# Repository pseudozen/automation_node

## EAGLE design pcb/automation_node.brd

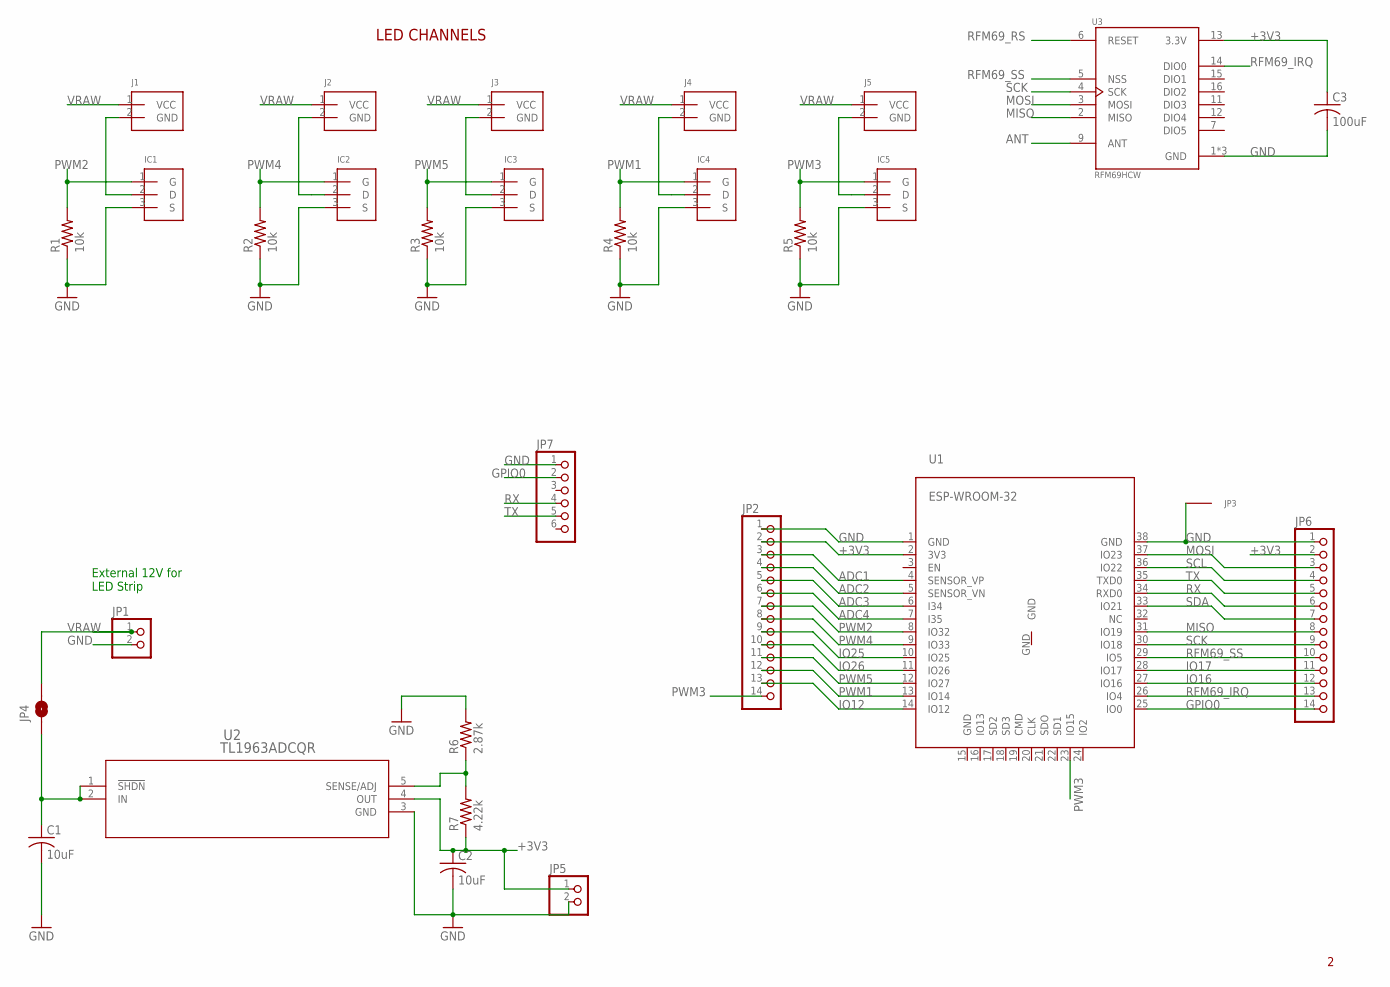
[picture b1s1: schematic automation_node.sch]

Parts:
C1, C2: 10uF; C0805
C3: 100uF; C0805
IC1, IC2, IC3, IC4, IC5: POWER_FET
J1, J2, J3, J4, J5: POWER-VIAS; 2CT-VIAS
JP1, JP5: PINHD-1X2; 1X02
JP2, JP6: PINHD-1X14; 1X14
JP3: PROTO_VIA_COMPACT; PROTO_VIA
JP4: JUMPER-SMT_2_NO_SILK; SMT-JUMPER_2_NO_SILK
JP7: PINHD-1X6; 1X06
R1, R2, R3, R4, R5: 10k; R0805
R6: 2.87k; R0805
R7: 4.22k; R0805
U1: ESP-WROOM-32
U2: TL1963ADCQR; DCQ6
U3: RFM69HCW; MOD_COM-13909

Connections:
+3V3: C2.1, C3.1, JP2.2, JP5.1, JP6.2, R7.1, U1.2 (3V3), U2.4 (OUT), U3.13 (3.3V)
ADC1: JP2.3, U1.4 (SENSOR_VP)
ADC2: JP2.4, U1.5 (SENSOR_VN)
ADC3: JP2.5, U1.6 (I34)
ADC4: JP2.6, U1.7 (I35)
ANT: U3.9 (ANT)
GND: C1.2, C2.2, C3.2, IC1.3 (S), IC2.3 (S), IC3.3 (S), IC4.3 (S), IC5.3 (S), JP1.2, JP2.1, JP3.1, JP5.2, JP6.1, JP7.1, R1.1, R2.1, R3.1, R4.1, R5.1, R6.2, U1.1 (GND), U1.38 (GND), U2.3 (GND), U3.1 (GND), U3.8 (GND), U3.10 (GND)
GPIO0: JP6.14, JP7.2, U1.25 (IO0)
IO12: JP2.13, U1.14 (IO12)
IO16: JP6.12, U1.27 (IO16)
IO17: JP6.11, U1.28 (IO17)
IO25: JP2.9, U1.10 (IO25)
IO26: JP2.10, U1.11 (IO26)
MISO: JP6.8, U1.31 (IO19), U3.2 (MISO)
MOSI: JP6.3, U1.37 (IO23), U3.3 (MOSI)
unnamed: IC1.2 (D), J1.2 (GND)
unnamed: IC2.2 (D), J2.2 (GND)
unnamed: IC3.2 (D), J3.2 (GND)
unnamed: IC4.2 (D), J4.2 (GND)
unnamed: IC5.2 (D), J5.2 (GND)
PWM1: IC4.1 (G), JP2.12, R4.2, U1.13 (IO14)
PWM2: IC1.1 (G), JP2.7, R1.2, U1.8 (IO32)
PWM3: IC5.1 (G), JP2.14, R5.2, U1.23 (IO15)
PWM4: IC2.1 (G), JP2.8, R2.2, U1.9 (IO33)
PWM5: IC3.1 (G), JP2.11, R3.2, U1.12 (IO27)
RFM69_IRQ: JP6.13, U1.26 (IO4), U3.14 (DIO0)
RFM69_RS: U3.6 (RESET)
RFM69_SS: JP6.10, U1.29 (IO5), U3.5 (NSS)
RX: JP6.6, JP7.4, U1.34 (RXD0)
SCK: JP6.9, U1.30 (IO18), U3.4 (SCK)
SCL: JP6.4, U1.36 (IO22)
SDA: JP6.7, U1.33 (IO21)
SHDN: C1.1, JP4.1, U2.1 (!SHDN), U2.2 (IN)
TX: JP6.5, JP7.5, U1.35 (TXD0)
U2_ADJ: R6.1, R7.2, U2.5 (SENSE/ADJ)
VRAW: J1.1 (VCC), J2.1 (VCC), J3.1 (VCC), J4.1 (VCC), J5.1 (VCC), JP1.1, JP4.2

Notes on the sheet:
LED CHANNELS
External 12V for LED Strip

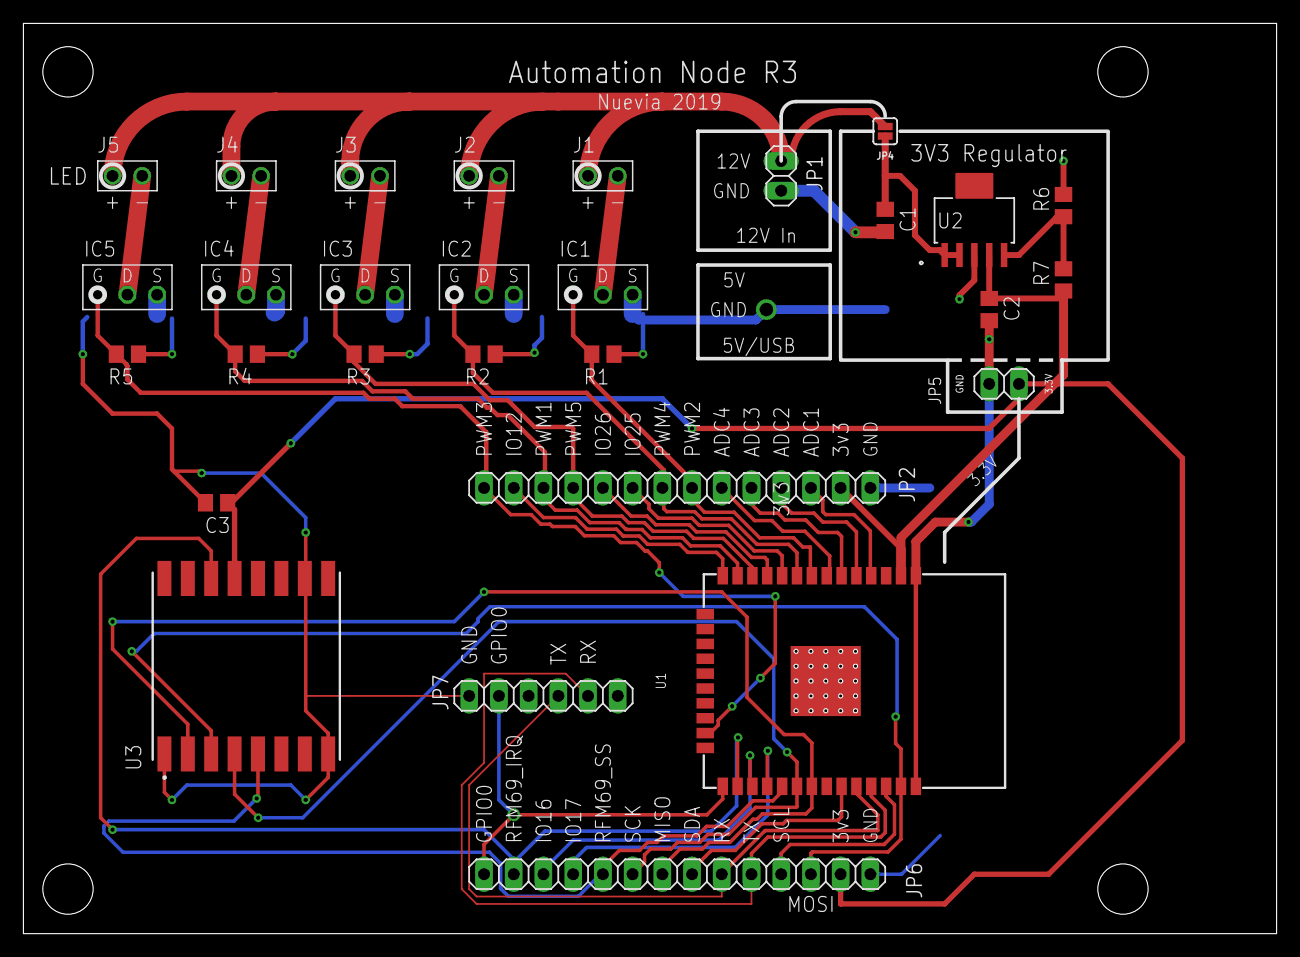
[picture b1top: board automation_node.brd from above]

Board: 2 copper layers, 107.1 x 77.8 mm, 30 parts (0 on the bottom side), 34 nets.

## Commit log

2019-07-10 added 3v3 regulator section; expanded board size to fit a Polycase enclosure, but mounting holes would cause lots of rerouting, so left it not matching any specific enclousure at this point
2019-07-19 added RFM69, finished routing all but RFM69
2019-07-19 added programming header for ESP32
2019-07-19 moved vias away from bottom side of rfm69
2019-07-19 added GPIO0 to programming header
2019-07-19 added R3 schematic pdf
2019-07-24 added test code for RFM69, for burn-in testing with structs, encryption, all other settings default
